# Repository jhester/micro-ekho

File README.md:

Micro Ekho
========

#### Summary
Micro Ekhos are simply miniature, battery powered, deployable versions of [Ekho](https://github.com/jhester/ekho) that can be put placed in energy environments of interest for extended periods of time. They transmit IV curve data over a Sub 1GHz frequency to a basestation, that collects and forwards to a desktop, a phone, or stores all data to an SD card.

This repo holds the hardware files, firmware (basestation, and node), mobile app viewing software (iOs, Android) and desktop viewing software, for Micro Ekho devices.

#### What is Ekho?
Ekho is a energy environment recorder, and emulator for the Internet of Things. It lets scientists and developers who work with tiny, batteryless, energy harevsting devices (think solar panels, piezos, peltier, RFID) have a repeatable testing environment. Without Ekho, verifying functionality for certain energy conditions, is impossible.

Our paper, "Ekho: Realistic and Repeatable Experimentation for Tiny Energy-Harvesting Sensors" describes the design and evaluation of a new tool for recording and replaying energy harvesting conditions. Energy harvesting is a necessity for many small, embedded sensing devices, that must operate maintenance-free for long periods of time. However, understanding how the environment changes and it's effects on device behavior has always been a source of frustration. Ekho allows system designers working with ultra low power devices, to realistically predict how new hardware and software configurations will perform before deployment. By taking advantage of electrical characteristics all energy sources share, Ekho is able to emulate many different energy sources (e.g., Solar, RF, Thermal, and Vibrational) and takes much of the guesswork out of experimentation with tiny, energy harvesting sensing systems.

This paper received the BEST PAPER Award at the 12th ACM Conference on Embedded Networked Sensor Systems (SenSys 2014).

For more information on the concept, design, and evaluation of Ekho, checkout [my website](http://josiahhester.comr).

#### Contents
The "basestation" aggregates the data from multiple "nodes," then sends this to the client application (which can be on a phone, tablet, or desktop) or logs to an SD card. Embedded C on a Teensy ARM chip.

The "desktop" folder contains an electron app that displays the data gathered.

The "hardware" folder contains all the EAGLE files for the micro ekho hardware.

The "mobile" renders the aggregate data on a screen, in real time. Written with apache cordova, HTML, CSS, JavaScript.

The "node" folder holds all the code for the Micro Ekho nodes that are attached to energy harvesters. These nodes send IV data to the "basestation" over the radio. Embedded C on an MSP430.

### Getting Started
Currently, this project is very much in progress, please contact me for more information, or raise an Issue.

#### License
Except for the desktop application made with Electron, everything else is MIT.

The MIT License (MIT)
Copyright (c) 2016 Josiah Hester

Permission is hereby granted, free of charge, to any person obtaining a copy of this software and associated documentation files (the "Software"), to deal in the Software without restriction, including without limitation the rights to use, copy, modify, merge, publish, distribute, sublicense, and/or sell copies of the Software, and to permit persons to whom the Software is furnished to do so, subject to the following conditions:

The above copyright notice and this permission notice shall be included in all copies or substantial portions of the Software.

THE SOFTWARE IS PROVIDED "AS IS", WITHOUT WARRANTY OF ANY KIND, EXPRESS OR IMPLIED, INCLUDING BUT NOT LIMITED TO THE WARRANTIES OF MERCHANTABILITY, FITNESS FOR A PARTICULAR PURPOSE AND NONINFRINGEMENT. IN NO EVENT SHALL THE AUTHORS OR COPYRIGHT HOLDERS BE LIABLE FOR ANY CLAIM, DAMAGES OR OTHER LIABILITY, WHETHER IN AN ACTION OF CONTRACT, TORT OR OTHERWISE, ARISING FROM, OUT OF OR IN CONNECTION WITH THE SOFTWARE OR THE USE OR OTHER DEALINGS IN THE SOFTWARE.

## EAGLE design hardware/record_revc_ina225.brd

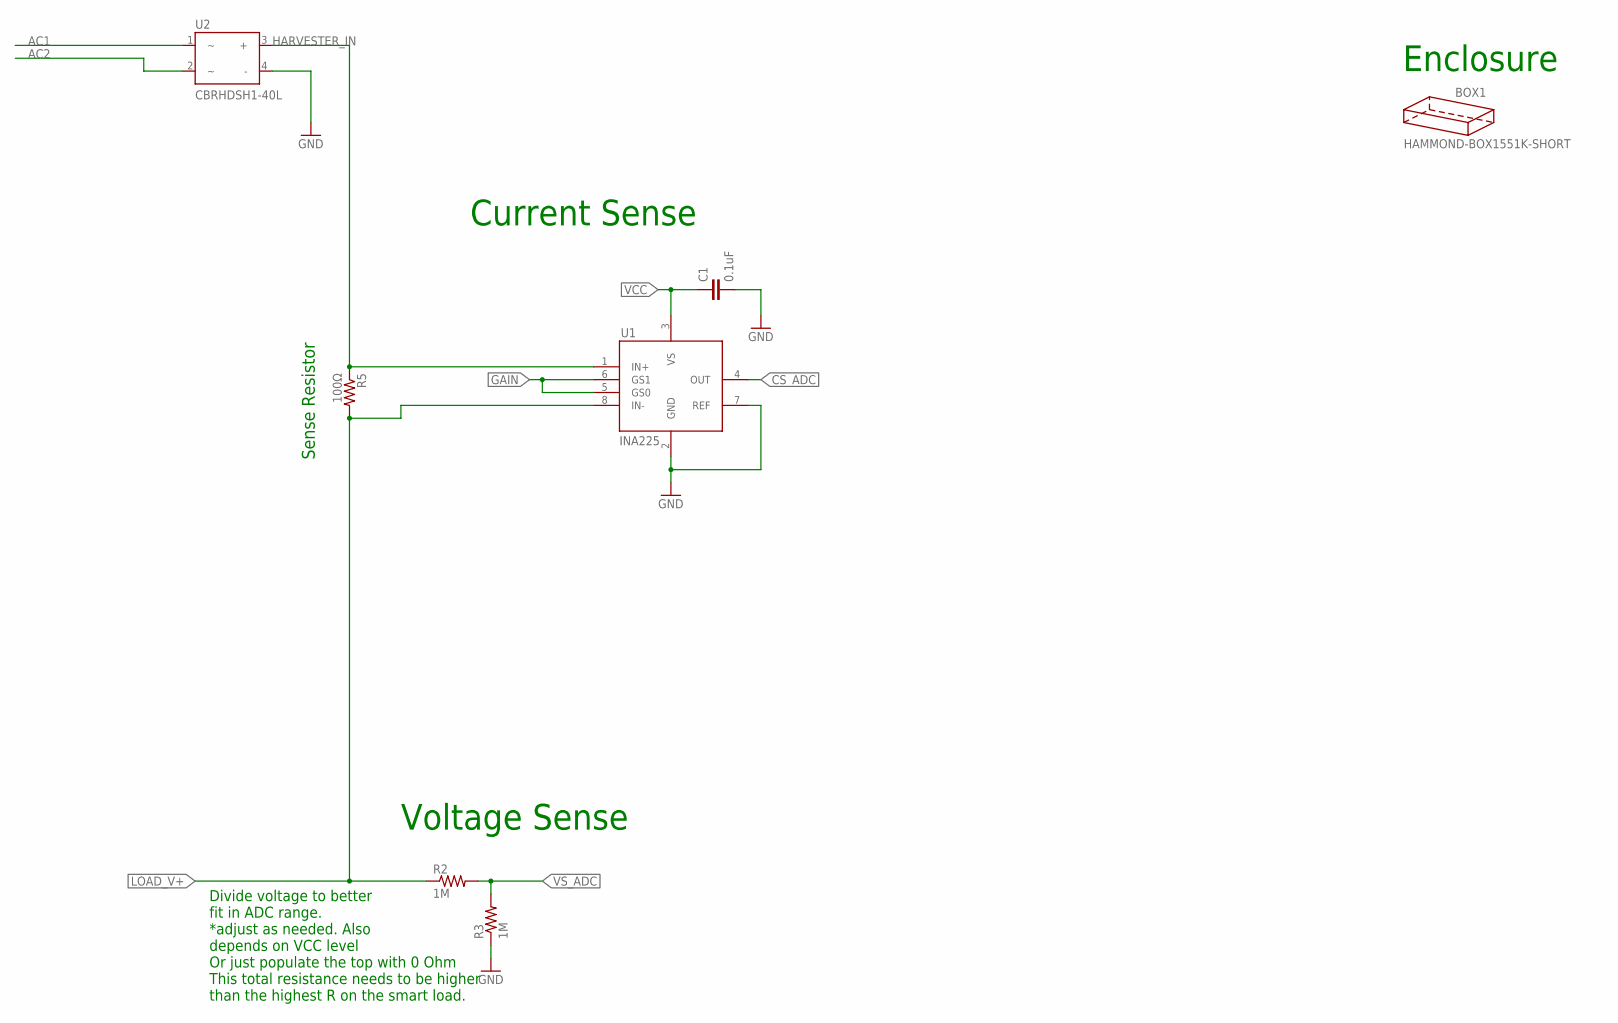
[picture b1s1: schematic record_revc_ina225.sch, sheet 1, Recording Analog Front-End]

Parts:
BOX1: HAMMOND-BOX1551K-SHORT; 1551K-SHORT
C1: 0.1uF; C0805
R2, R3: 1M; 0805
R5: 100Ω; 0805
U1: INA225; MSOP8
U2: CBRHDSH1-40L; HD_DIP4

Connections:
AC1: U2.1; also elsewhere on the board
AC2: U2.2; also elsewhere on the board
CS_ADC: U1.4 (OUT); also elsewhere on the board
GAIN: U1.5 (GS0), U1.6 (GS1); also elsewhere on the board
GND: C1.2, R3.1, U1.2 (GND), U1.7 (REF), U2.4 (-); also elsewhere on the board
HARVESTER_IN: R5.1, U1.1 (IN+), U2.3 (+); also elsewhere on the board
LOAD_V+: R2.1, R5.2, U1.8 (IN-); also elsewhere on the board
VCC: C1.1, U1.3 (VS); also elsewhere on the board
VS_ADC: R2.2, R3.2; also elsewhere on the board

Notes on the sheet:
Sense Resistor
Voltage Sense
Current Sense
Divide voltage to better fit in ADC range. *adjust as needed. Also depends on VCC level Or just populate the top with 0 Ohm This total resistance needs to be higher than the highest R on the smart load.
Enclosure

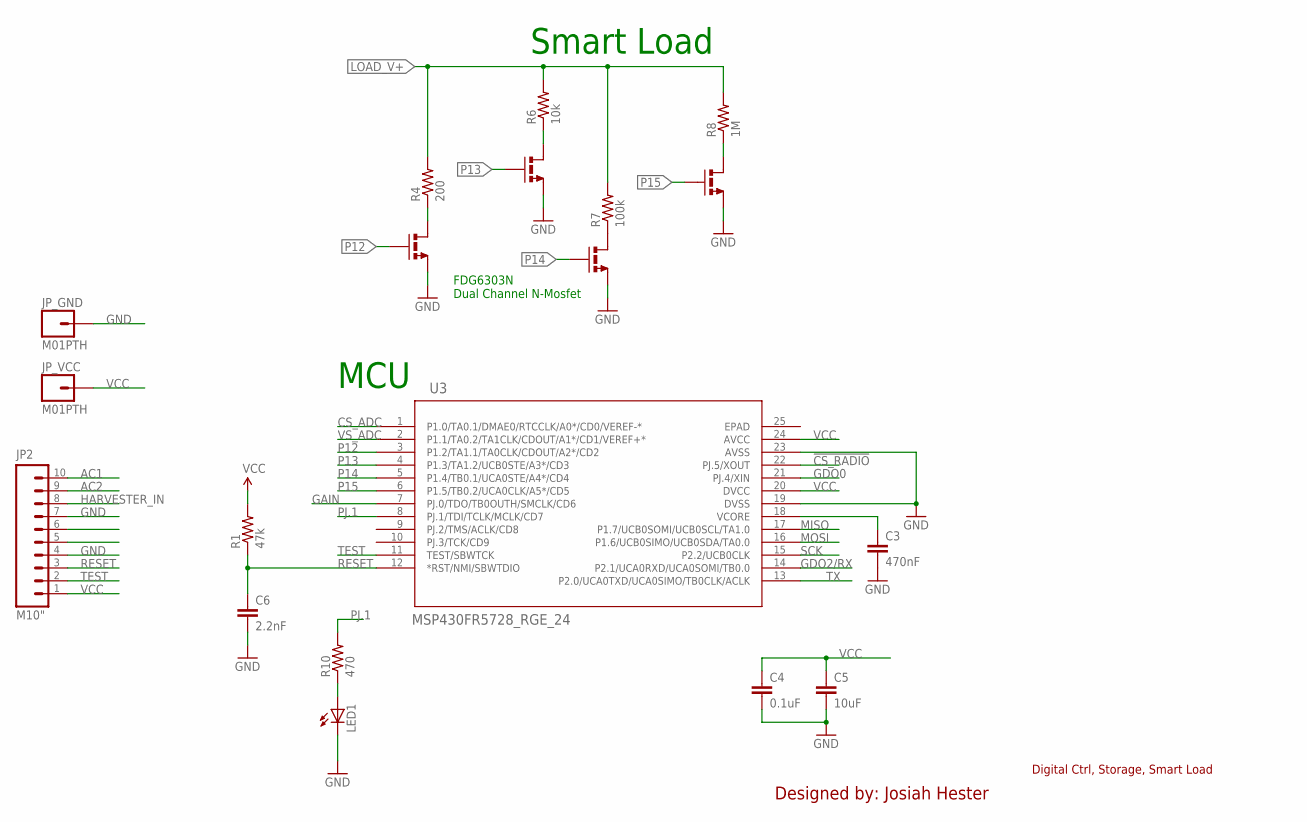
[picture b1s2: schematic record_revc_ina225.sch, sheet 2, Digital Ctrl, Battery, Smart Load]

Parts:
C3: 470nF; 0805
C4: 0.1uF; 0805
C5: 10uF; 0805
C6: 2.2nF; 0805
JP2: M10"; 1X10
JP_GND: M01PTH; 1X01
JP_VCC: M01PTH; 1X01
LED1: LED0603; LED-0603
R1: 47k; 0805
R4: 200; 0805
R6: 10k; 0805
R7: 100k; 0805
R8: 1M; 0805
R10: 470; 0805
U3: MSP430FR5728_RGE_24; RGE24_2P1X2P1
U4, U5: FDG6303N; SC70-6

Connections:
!CS_RADIO: U3.22 (PJ.5/XOUT); also elsewhere on the board
AC1: JP2.10; also elsewhere on the board
AC2: JP2.9; also elsewhere on the board
CS_ADC: U3.1 (P1.0/TA0.1/DMAE0/RTCCLK/A0*/CD0/VEREF-*); also elsewhere on the board
GAIN: U3.7 (PJ.0/TDO/TB0OUTH/SMCLK/CD6); also elsewhere on the board
GDO0: U3.21 (PJ.4/XIN); also elsewhere on the board
GDO2/RX: JP2.6, U3.14 (P2.1/UCA0RXD/UCA0SOMI/TB0.0); also elsewhere on the board
GND: C3.2, C4.2, C5.2, C6.2, JP2.4, JP2.7, JP_GND.1, LED1.C, U3.19 (DVSS), U3.23 (AVSS), U4.1 (S2), U4.4 (S1), U5.1 (S2), U5.4 (S1); also elsewhere on the board
HARVESTER_IN: JP2.8; also elsewhere on the board
LOAD_V+: R4.2, R6.2, R7.2, R8.2; also elsewhere on the board
MISO: U3.17 (P1.7/UCB0SOMI/UCB0SCL/TA1.0); also elsewhere on the board
MOSI: U3.16 (P1.6/UCB0SIMO/UCB0SDA/TA0.0); also elsewhere on the board
unnamed: C3.1, U3.18 (VCORE)
unnamed: R7.1, U5.3 (D1)
unnamed: R8.1, U5.6 (D2)
unnamed: R6.1, U4.6 (D2)
unnamed: R4.1, U4.3 (D1)
unnamed: LED1.A, R10.1
P12: U3.3 (P1.2/TA1.1/TA0CLK/CDOUT/A2*/CD2), U4.5 (G1)
P13: U3.4 (P1.3/TA1.2/UCB0STE/A3*/CD3), U4.2 (G2)
P14: U3.5 (P1.4/TB0.1/UCA0STE/A4*/CD4), U5.5 (G1)
P15: U3.6 (P1.5/TB0.2/UCA0CLK/A5*/CD5), U5.2 (G2)
PJ.1: R10.2, U3.8 (PJ.1/TDI/TCLK/MCLK/CD7)
RESET: C6.1, JP2.3, R1.1, U3.12 (*RST/NMI/SBWTDIO)
SCK: U3.15 (P2.2/UCB0CLK); also elsewhere on the board
TEST: JP2.2, U3.11 (TEST/SBWTCK)
TX: JP2.5, U3.13 (P2.0/UCA0TXD/UCA0SIMO/TB0CLK/ACLK)
VCC: C4.1, C5.1, JP2.1, JP_VCC.1, R1.2, U3.20 (DVCC), U3.24 (AVCC); also elsewhere on the board
VS_ADC: U3.2 (P1.1/TA0.2/TA1CLK/CDOUT/A1*/CD1/VEREF+*); also elsewhere on the board

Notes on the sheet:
Digital Ctrl, Storage, Smart Load
Designed by: Josiah Hester
MCU
Smart Load
FDG6303N Dual Channel N-Mosfet

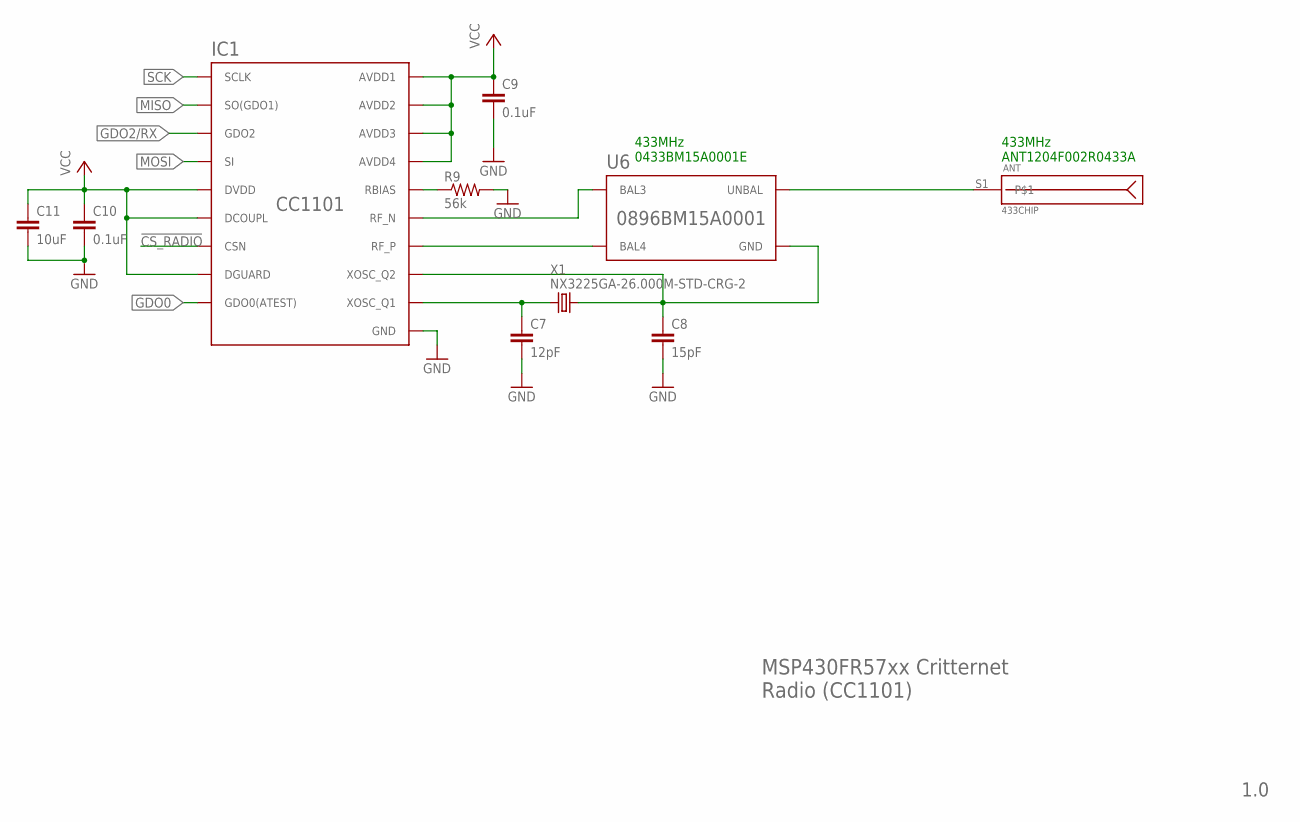
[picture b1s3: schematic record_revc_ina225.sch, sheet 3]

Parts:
ANT: 433CHIP; ANT-433-USP
C7: 12pF; 0603-CAP
C8: 15pF; 0603-CAP
C9: 0.1uF; 0603-CAP
C10: 0.1uF; C0805
C11: 10uF; 0805
IC1: CC1101; QLP20
R9: 56k; 0603
U6: 0896BM15A0001
X1: NX3225GA-26.000M-STD-CRG-2; XTAL-3.2X2.5

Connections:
!CS_RADIO: IC1.7 (CSN); also elsewhere on the board
GDO0: IC1.6 (GDO0(ATEST)); also elsewhere on the board
GDO2/RX: IC1.3 (GDO2); also elsewhere on the board
GND: C7.2, C8.2, C9.2, C10.2, C11.2, IC1.16 (GND), IC1.19 (GND), IC1.GND, IC1.GND1 (GND), IC1.GND2 (GND), IC1.GND3 (GND), IC1.GND4 (GND), IC1.GND5 (GND), R9.2; also elsewhere on the board
MISO: IC1.2 (SO(GDO1)); also elsewhere on the board
MOSI: IC1.20 (SI); also elsewhere on the board
unnamed: IC1.12 (RF_P), U6.4 (BAL4)
unnamed: IC1.13 (RF_N), U6.3 (BAL3)
unnamed: C7.1, IC1.8 (XOSC_Q1), X1.1
unnamed: IC1.17 (RBIAS), R9.1
unnamed: ANT.S1, U6.1 (UNBAL)
SCK: IC1.1 (SCLK); also elsewhere on the board
VCC: C9.1, C10.1, C11.1, IC1.4 (DVDD), IC1.5 (DCOUPL), IC1.9 (AVDD1), IC1.11 (AVDD2), IC1.14 (AVDD3), IC1.15 (AVDD4), IC1.18 (DGUARD); also elsewhere on the board
XOSC_Q2: C8.1, IC1.10 (XOSC_Q2), U6.2 (GND), U6.5 (GND), U6.6 (GND), X1.3 (2)

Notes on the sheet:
433MHz 0433BM15A0001E
MSP430FR57xx Critternet Radio (CC1101)
1.0
433MHz ANT1204F002R0433A

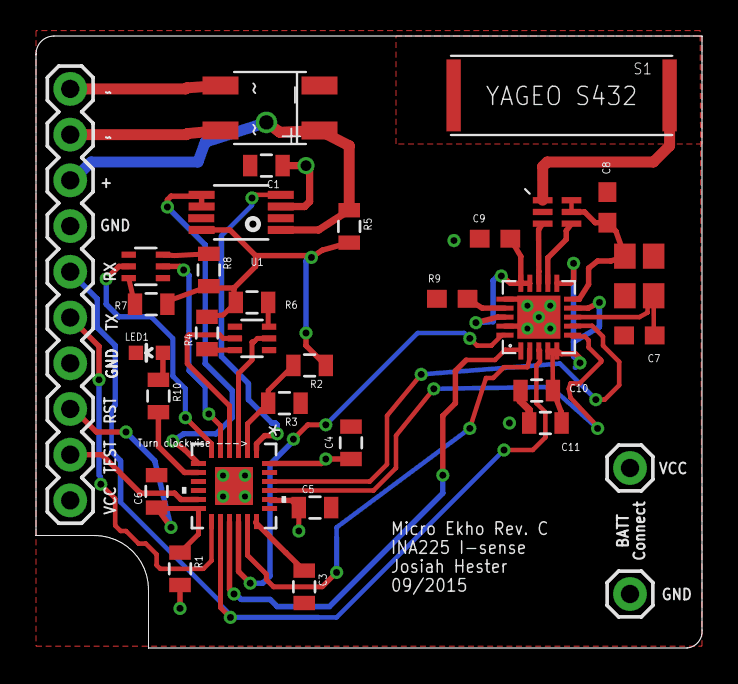
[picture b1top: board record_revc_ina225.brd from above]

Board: 4 copper layers, 37.0 x 34.0 mm, 34 parts (0 on the bottom side), 35 nets.

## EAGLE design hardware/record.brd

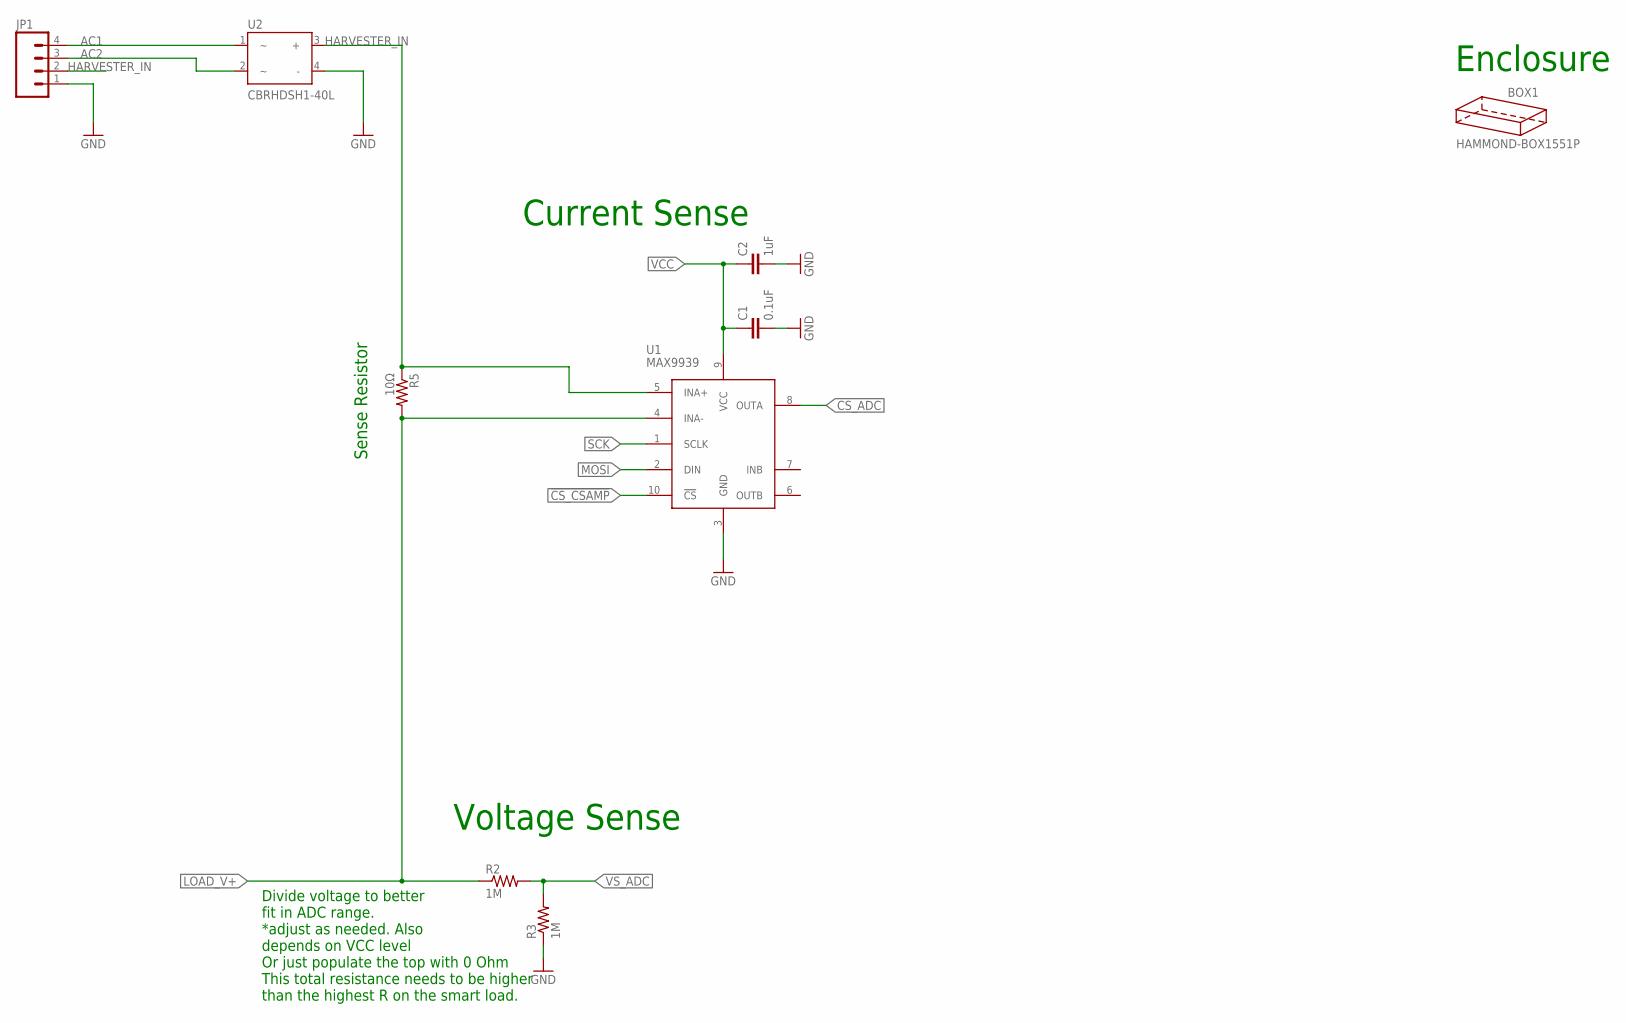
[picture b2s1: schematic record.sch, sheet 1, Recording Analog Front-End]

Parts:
BOX1: HAMMOND-BOX1551P; 1551P
C1: 0.1uF; C0805
C2: 1uF; C0805
JP1: M04PTH; 1X04
R2, R3: 1M; 0805
R5: 10Ω; 0805
U1: MAX9939; 10µMAX
U2: CBRHDSH1-40L; HD_DIP4

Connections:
!CS_CSAMP: U1.10 (!CS); also elsewhere on the board
AC1: JP1.4, U2.1
AC2: JP1.3, U2.2
CS_ADC: U1.8 (OUTA); also elsewhere on the board
GND: C1.2, C2.2, JP1.1, R3.1, U1.3 (GND), U2.4 (-); also elsewhere on the board
HARVESTER_IN: JP1.2, R5.1, U1.5 (INA+), U2.3 (+)
LOAD_V+: R2.1, R5.2, U1.4 (INA-); also elsewhere on the board
MOSI: U1.2 (DIN); also elsewhere on the board
SCK: U1.1 (SCLK); also elsewhere on the board
VCC: C1.1, C2.1, U1.9 (VCC); also elsewhere on the board
VS_ADC: R2.2, R3.2; also elsewhere on the board

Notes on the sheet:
Sense Resistor
Voltage Sense
Current Sense
Divide voltage to better fit in ADC range. *adjust as needed. Also depends on VCC level Or just populate the top with 0 Ohm This total resistance needs to be higher than the highest R on the smart load.
Enclosure

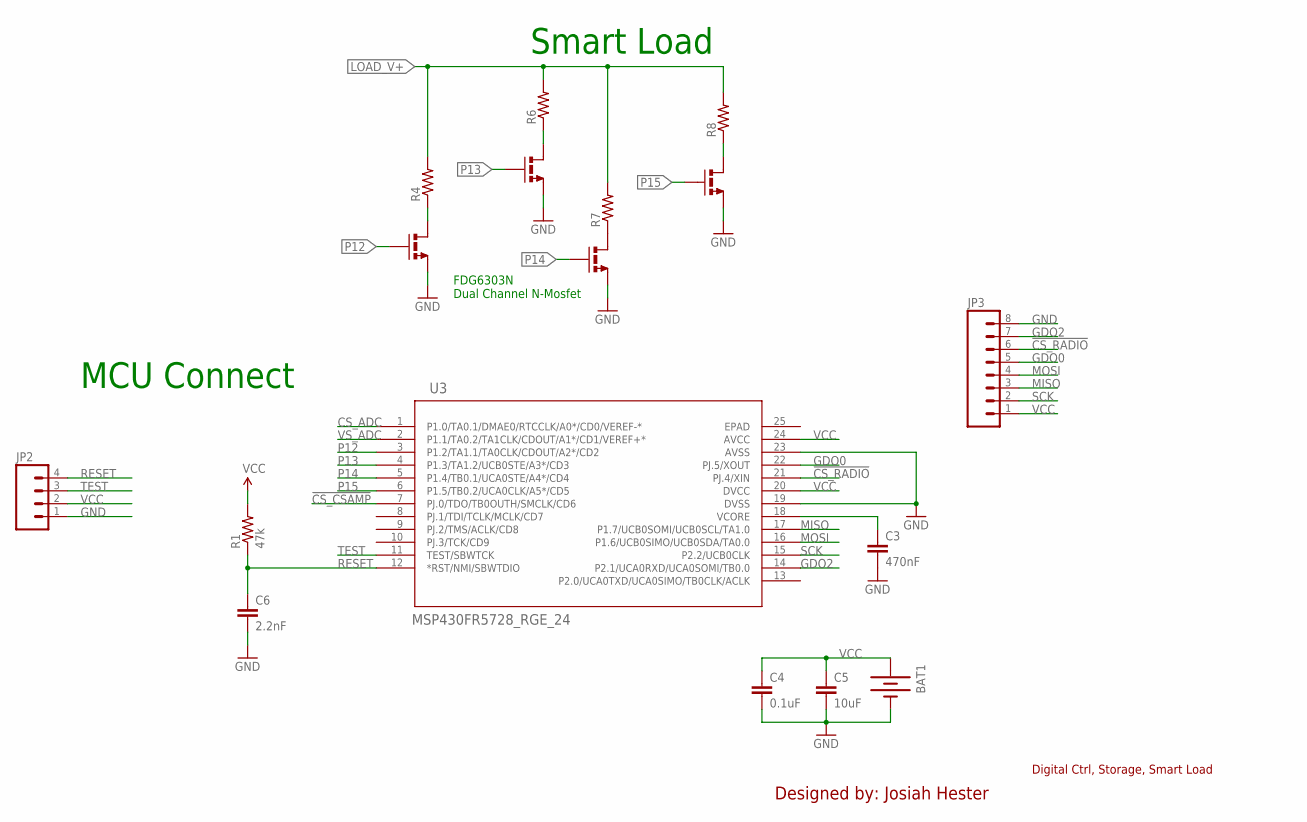
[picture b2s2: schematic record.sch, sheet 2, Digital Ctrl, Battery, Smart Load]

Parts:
BAT1: BATTERY20PTH; BATTCOM_20MM_PTH
C3: 470nF; 0805
C4: 0.1uF; 0805
C5: 10uF; 0805
C6: 2.2nF; 0805
JP2: M04PTH; 1X04
JP3: M081X08-1.27MM-PTH; 1X08-1.27MM
R1: 47k; 0805
R4, R6, R7, R8: 0.22OHM1/4W1%(0805); 0805
U3: MSP430FR5728_RGE_24; RGE24_2P1X2P1
U4, U5: FDG6303N; SC70-6

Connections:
!CS_CSAMP: U3.7 (PJ.0/TDO/TB0OUTH/SMCLK/CD6); also elsewhere on the board
!CS_RADIO: JP3.6, U3.21 (PJ.4/XIN)
CS_ADC: U3.1 (P1.0/TA0.1/DMAE0/RTCCLK/A0*/CD0/VEREF-*); also elsewhere on the board
GDO0: JP3.5, U3.22 (PJ.5/XOUT)
GDO2: JP3.7, U3.14 (P2.1/UCA0RXD/UCA0SOMI/TB0.0)
GND: BAT1.2 (-), C3.2, C4.2, C5.2, C6.2, JP2.1, JP3.8, U3.19 (DVSS), U3.23 (AVSS), U4.1 (S2), U4.4 (S1), U5.1 (S2), U5.4 (S1); also elsewhere on the board
LOAD_V+: R4.2, R6.2, R7.2, R8.2; also elsewhere on the board
MISO: JP3.3, U3.17 (P1.7/UCB0SOMI/UCB0SCL/TA1.0)
MOSI: JP3.4, U3.16 (P1.6/UCB0SIMO/UCB0SDA/TA0.0); also elsewhere on the board
unnamed: C3.1, U3.18 (VCORE)
unnamed: R7.1, U5.3 (D1)
unnamed: R8.1, U5.6 (D2)
unnamed: R6.1, U4.6 (D2)
unnamed: R4.1, U4.3 (D1)
P12: U3.3 (P1.2/TA1.1/TA0CLK/CDOUT/A2*/CD2), U4.5 (G1)
P13: U3.4 (P1.3/TA1.2/UCB0STE/A3*/CD3), U4.2 (G2)
P14: U3.5 (P1.4/TB0.1/UCA0STE/A4*/CD4), U5.5 (G1)
P15: U3.6 (P1.5/TB0.2/UCA0CLK/A5*/CD5), U5.2 (G2)
RESET: C6.1, JP2.4, R1.1, U3.12 (*RST/NMI/SBWTDIO)
SCK: JP3.2, U3.15 (P2.2/UCB0CLK); also elsewhere on the board
TEST: JP2.3, U3.11 (TEST/SBWTCK)
VCC: BAT1.1 (+), C4.1, C5.1, JP2.2, JP3.1, R1.2, U3.20 (DVCC), U3.24 (AVCC); also elsewhere on the board
VS_ADC: U3.2 (P1.1/TA0.2/TA1CLK/CDOUT/A1*/CD1/VEREF+*); also elsewhere on the board

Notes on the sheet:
Digital Ctrl, Storage, Smart Load
Designed by: Josiah Hester
MCU Connect
Smart Load
FDG6303N Dual Channel N-Mosfet

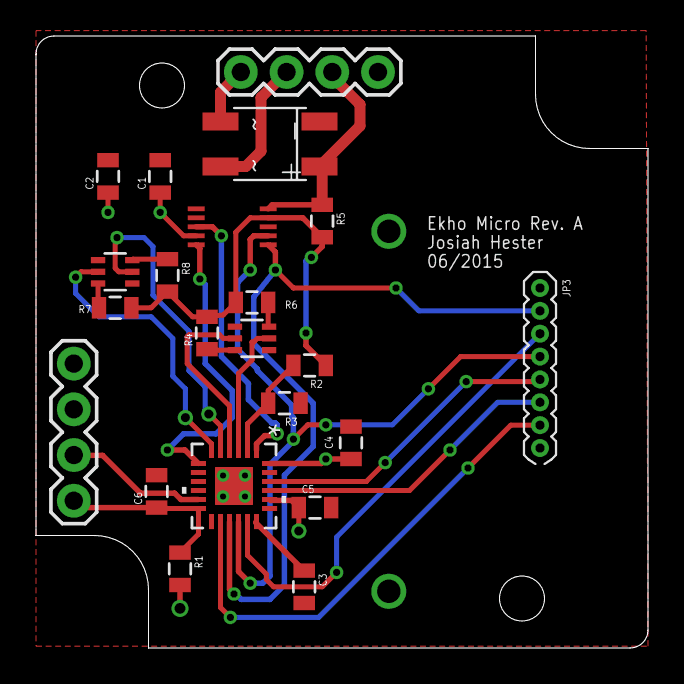
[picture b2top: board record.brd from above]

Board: 4 copper layers, 34.0 x 34.0 mm, 24 parts (1 on the bottom side), 26 nets.

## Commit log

2015-06-27 Put hardware, firmware, and software in one place for micro ecko.
2015-06-27 Added in control for the micro echo circuitry
2015-06-27 Starter basestation code for Teensy.
2015-07-03 Mostly works, data works from node, to basestation, to client, app works on bluetooth with BLE mini on Android
2015-07-06 Radios now work.
2015-07-09 App look and UI functionality pretty much all done for demo. Rewrote duty cycle with basestation to listen for a time on each channel. Changed node code to broadcast on a single channel every 100ms. 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
2015-07-10 Final demo for California. Everything works well. Four nodes stress test worked great. Not awesome with quick changing energy harvesters like piezo though.
2015-07-10 Added icons and branding.
2015-07-11 Made scaling better (to see small values) Added label on header to see the last value Added config settings to remove the over scroll in iOS, to keep the app in fullscreen, and to have the orientatio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
2015-07-20 Works for iOS now.
2015-12-21 New hardware, new software for clients.
2015-12-21 Added new code. This works. Archived / moved the mobile app code.
2015-12-22 Version 0.1 ----- CHANGELOG: - Added pause / resume button on upper right - Added radio selection for displaying Current, Voltage, or Power - Added axis labels to graphs - Added radio selection for d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
2015-12-22 Added TODOLIST
2016-01-25 Final hardware for circuit hub
2016-01-25 New basestation code
2016-01-26 Updated README again
2016-01-26 Updated README again again
2016-01-26 Updated package.json to include all deps

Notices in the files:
parts and their libraries:
SparkFun-Capacitors: Licensing: CC v3.0 Share-Alike You are welcome to use this library for commercial purposes.
